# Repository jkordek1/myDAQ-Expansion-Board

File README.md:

# myDAQ Expansion Board

 Expansion board for NI myDAQ Student Data Acquisition Device, developed in 2022 for students studying at Zagreb university of applied sciences.
 It enables quick and easy .VI development without the need of connecting different modules via breadboard and jumpers.
 
 ## Features
 - Push buttons
 - Toggle switches
 - LEDs
 - BCD decoder for seven-segment display
 - L298n H-bridge used for powering two DC motors or one stepper motor
 - ACS712ELCTR-05B-T current sense IC for motor current measurement
 - External power supply for DC motors
 - Potentiometer
 - Light dependent resistor

## Images

## Project folder structure
    .
    ├── ...
    ├── 3DPrint                 # Files for 3D printing
    ├── Images                  # Images of the project
    ├── KiCADFiles              # Main folder
    │   ├── 3d models           # 3d models of components
    │   ├── Datasheet           # Datasheet collection
    │   ├── Graphics            # Custom graphics for PCB
    │   ├── gerber              # gerber output folder
    │   ├── myDAQExpansionBoard # Main folder for KiCAD files
    │   └── Schematic.pdf       # Project schematic
    └── ...

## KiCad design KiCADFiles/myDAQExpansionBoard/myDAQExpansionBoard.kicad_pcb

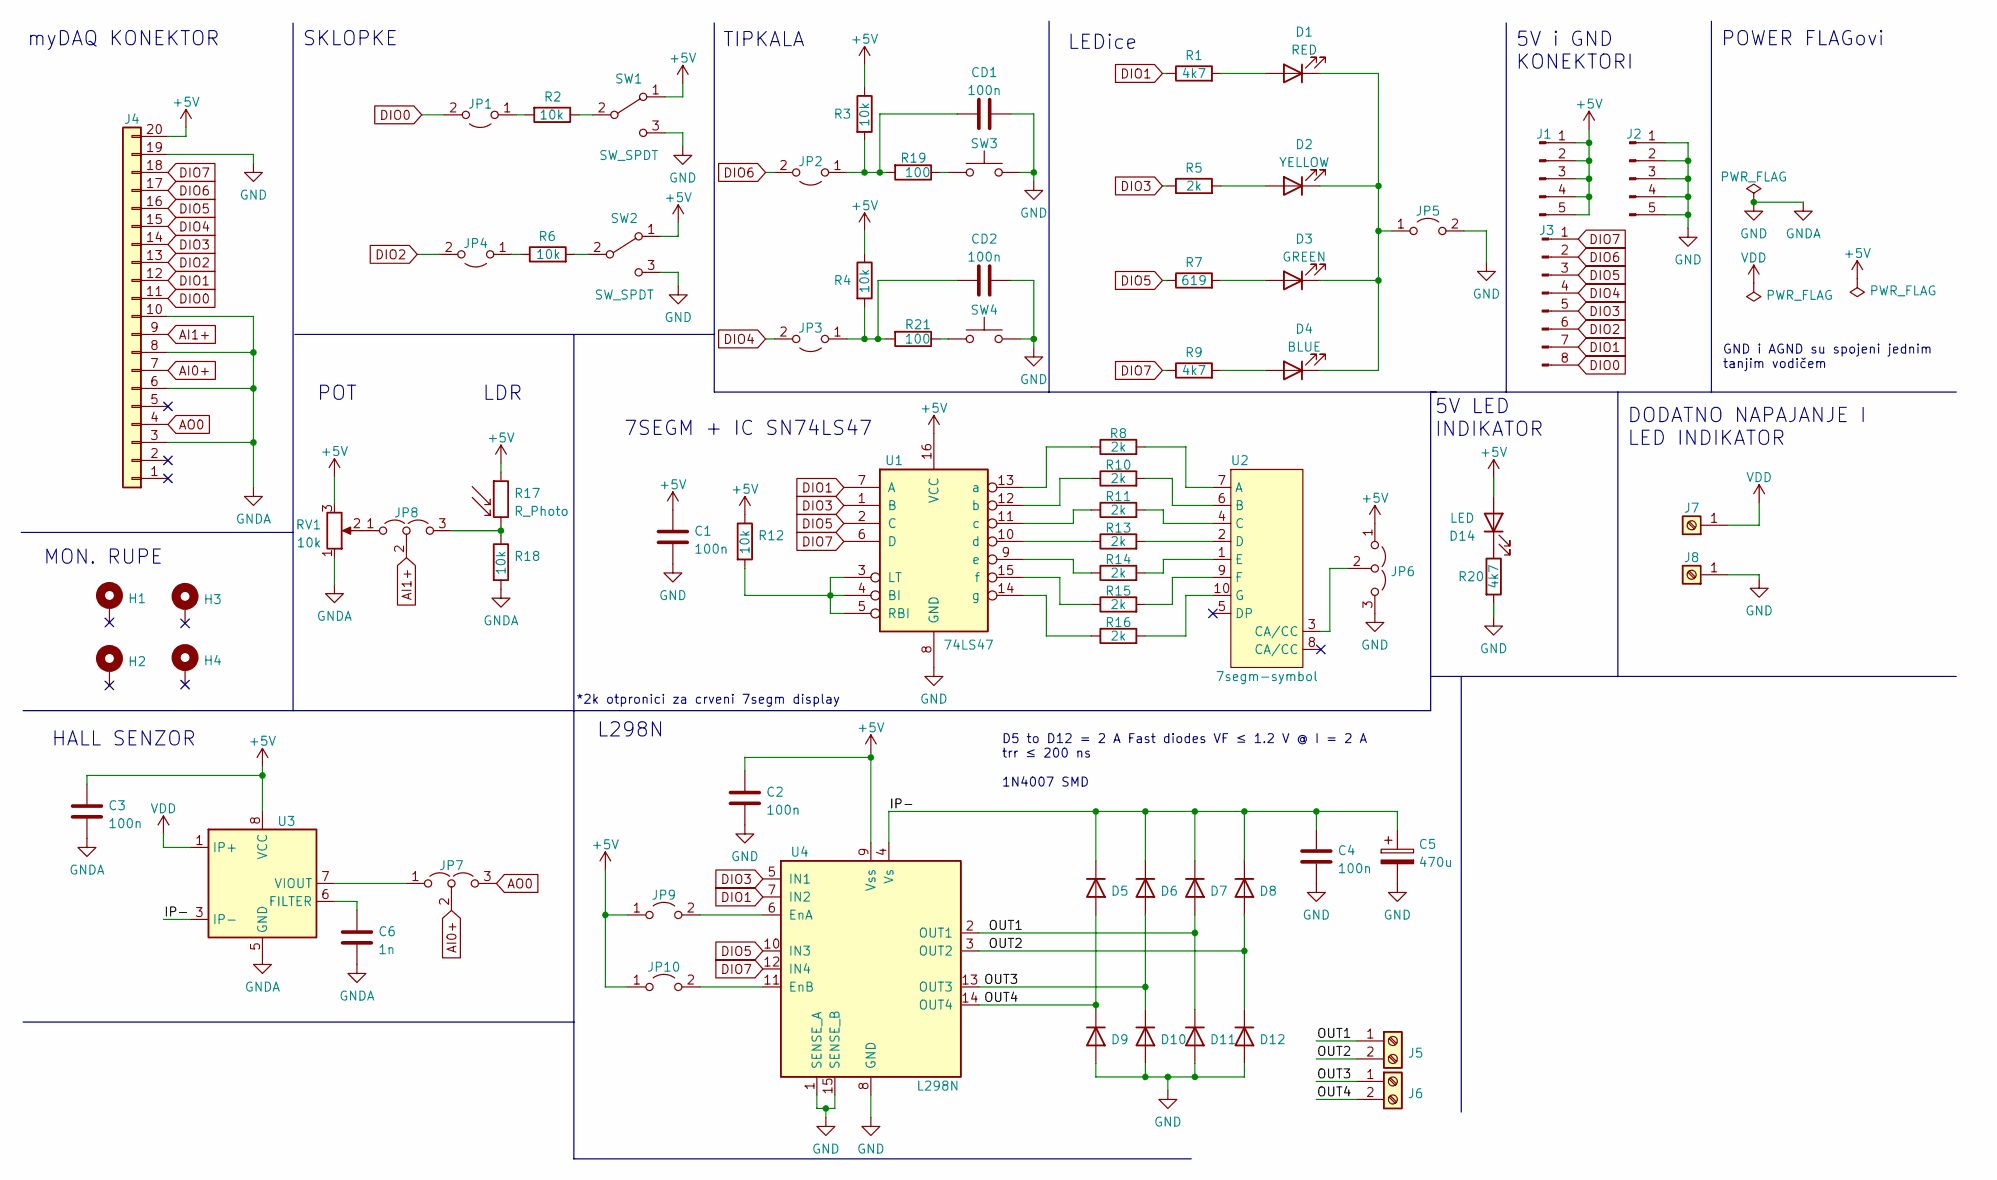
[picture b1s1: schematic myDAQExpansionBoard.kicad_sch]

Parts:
C1, C2, C3, C4: 100n; C_0603_1608Metric
C5: 470u; C_Radial_D10.0mm_H16.0mm_P5.00mm
C6: 1n; C_0603_1608Metric
CD1, CD2: 100n; C_0805_2012Metric
D1: RED; LED_D5.0mm
D2: YELLOW; LED_D5.0mm
D3: GREEN; LED_D5.0mm
D4: BLUE; LED_D5.0mm
D5, D6, D7, D8, D9, D10, D11, D12: 1N4007; D_SMA
D14: LED; LED_1206_3216Metric
H1, H2, H3, H4: MountingHole_Pad; MountingHole_3.2mm_M3_ISO7380_Pad
J1, J2: Conn_01x05_Male; PinHeader_1x05_P2.54mm_Vertical
J3: Conn_01x08_Male; PinHeader_1x08_P2.54mm_Vertical
J4: OSTV7XX3151
J5, J6: Screw_Terminal_01x02; TerminalBlock_Phoenix_MKDS-1,5-2-5.08_1x02_P5.08mm_Horizont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
J7: Screw_Terminal_01x01; DELTRON 4mm banana socket - red
J8: Screw_Terminal_01x01; DELTRON 4mm banana socket - black
JP1, JP2, JP3, JP4, JP5, JP9, JP10: Jumper_2_Open; PinHeader_1x02_P2.54mm_jumper
JP6, JP7, JP8: Jumper_3_Open; PinHeader_1x03_P2.54mm_Vertical_jumper
R1, R9, R20: 4k7; R_0603_1608Metric
R2, R3, R4, R6, R12, R18: 10k; R_0603_1608Metric
R5, R8, R10, R11, R13, R14, R15, R16: 2k; R_0603_1608Metric
R7: 619; R_0603_1608Metric
R17: R_Photo; R_LDR_5.1x4.3mm_P3.4mm_Vertical
R19, R21: 100; R_0603_1608Metric
RV1: 10k; PTV09A-4225F-B502
SW1, SW2: SW_SPDT; EG1271A
SW3, SW4: SW_Push; Omron_B3F-12x12mm
U1: 74LS47; DIP-16_W7.62mm
U2: 7segm-symbol; 7segm-SA52
U3: ACS712xLCTR-05B; SOIC-8_3.9x4.9mm_P1.27mm
U4: L298N; L298n

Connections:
+5V: C1.1, C2.1, C3.1, D14.2 (A), J1.1, J1.2, J1.3, J1.4, J1.5, J4.20, JP6.1 (A), JP9.1 (A), JP10.1 (A), R3.1, R4.1, R12.1, R17.1, RV1.3, SW1.1 (A), SW2.1 (A), U1.16 (VCC), U3.8 (VCC), U4.9 (Vss)
/IP-: C4.1, C5.1, D5.1 (K), D6.1 (K), D7.1 (K), D8.1 (K), U3.3 (IP-), U3.4 (IP-), U4.4 (Vs)
/OUT1: D7.2 (A), D11.1 (K), J5.1, U4.2 (OUT1)
/OUT2: D8.2 (A), D12.1 (K), J5.2, U4.3 (OUT2)
/OUT3: D6.2 (A), D10.1 (K), J6.1, U4.13 (OUT3)
/OUT4: D5.2 (A), D9.1 (K), J6.2, U4.14 (OUT4)
AI0+: J4.7, JP7.2 (C)
AI1+: J4.9, JP8.2 (C)
AO0: J4.4, JP7.3 (B)
DIO0: J3.8, J4.11, JP1.2 (B)
DIO1: J3.7, J4.12, R1.1, U1.7 (A), U4.7 (IN2)
DIO2: J3.6, J4.13, JP4.2 (B)
DIO3: J3.5, J4.14, R5.1, U1.1 (B), U4.5 (IN1)
DIO4: J3.4, J4.15, JP3.2 (B)
DIO5: J3.3, J4.16, R7.1, U1.2 (C), U4.10 (IN3)
DIO6: J3.2, J4.17, JP2.2 (B)
DIO7: J3.1, J4.18, R9.1, U1.6 (D), U4.12 (IN4)
GND: C1.2, C2.2, C3.2, C4.2, C5.2, C6.2, CD1.2, CD2.2, D9.2 (A), D10.2 (A), D11.2 (A), D12.2 (A), J2.1, J2.2, J2.3, J2.4, J2.5, J4.3, J4.6, J4.8, J4.10, J4.19, J8.1, JP5.2 (B), JP6.3 (B), R18.2, R20.2, RV1.1, SW1.3 (C), SW2.3 (C), SW3.2, SW4.2, U1.8 (GND), U3.5 (GND), U4.1 (SENSE_A), U4.8 (GND), U4.15 (SENSE_B)
unnamed: C6.1, U3.6 (FILTER)
unnamed: CD1.1, JP2.1 (A), R3.2, R19.2
unnamed: CD2.1, JP3.1 (A), R4.2, R21.2
unnamed: D1.1 (K), D2.1 (K), D3.1 (K), D4.1 (K), JP5.1 (A)
unnamed: D1.2 (A), R1.2
unnamed: D2.2 (A), R5.2
unnamed: D3.2 (A), R7.2
unnamed: D4.2 (A), R9.2
unnamed: D14.1 (K), R20.1
unnamed: JP1.1 (A), R2.2
unnamed: JP4.1 (A), R6.1
unnamed: JP6.2 (C), U2.3 (CA/CC)
unnamed: JP7.1 (A), U3.7 (VIOUT)
unnamed: JP8.1 (A), RV1.2
unnamed: JP8.3 (B), R17.2, R18.1
unnamed: JP9.2 (B), U4.6 (EnA)
unnamed: JP10.2 (B), U4.11 (EnB)
unnamed: R2.1, SW1.2 (B)
unnamed: R6.2, SW2.2 (B)
unnamed: R8.1, U1.13 (a)
unnamed: R8.2, U2.7 (A)
unnamed: R10.1, U1.12 (b)
unnamed: R10.2, U2.6 (B)
unnamed: R11.1, U1.11 (c)
unnamed: R11.2, U2.4 (C)
unnamed: R12.2, U1.3 (LT), U1.4 (BI), U1.5 (RBI)
unnamed: R13.1, U1.10 (d)
unnamed: R13.2, U2.2 (D)
unnamed: R14.1, U1.9 (e)
unnamed: R14.2, U2.1 (E)
unnamed: R15.1, U1.15 (f)
unnamed: R15.2, U2.9 (F)
unnamed: R16.1, U1.14 (g)
unnamed: R16.2, U2.10 (G)
unnamed: R19.1, SW3.1
unnamed: R21.1, SW4.1
VDD: J7.1, U3.1 (IP+), U3.2 (IP+)

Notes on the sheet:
myDAQ KONEKTOR
LEDice
5V LED INDIKATOR
*2k otpronici za crveni 7segm display
D5 to D12 = 2 A Fast diodes VF ≤ 1.2 V @ I = 2 A trr ≤ 200 ns 1N4007 SMD
5V i GND KONEKTORI
7SEGM + IC SN74LS47
POT
HALL SENZOR
POWER FLAGovi
L298N
MON. RUPE
TIPKALA
SKLOPKE
DODATNO NAPAJANJE I LED INDIKATOR
GND i AGND su spojeni jednim tanjim vodičem
LDR

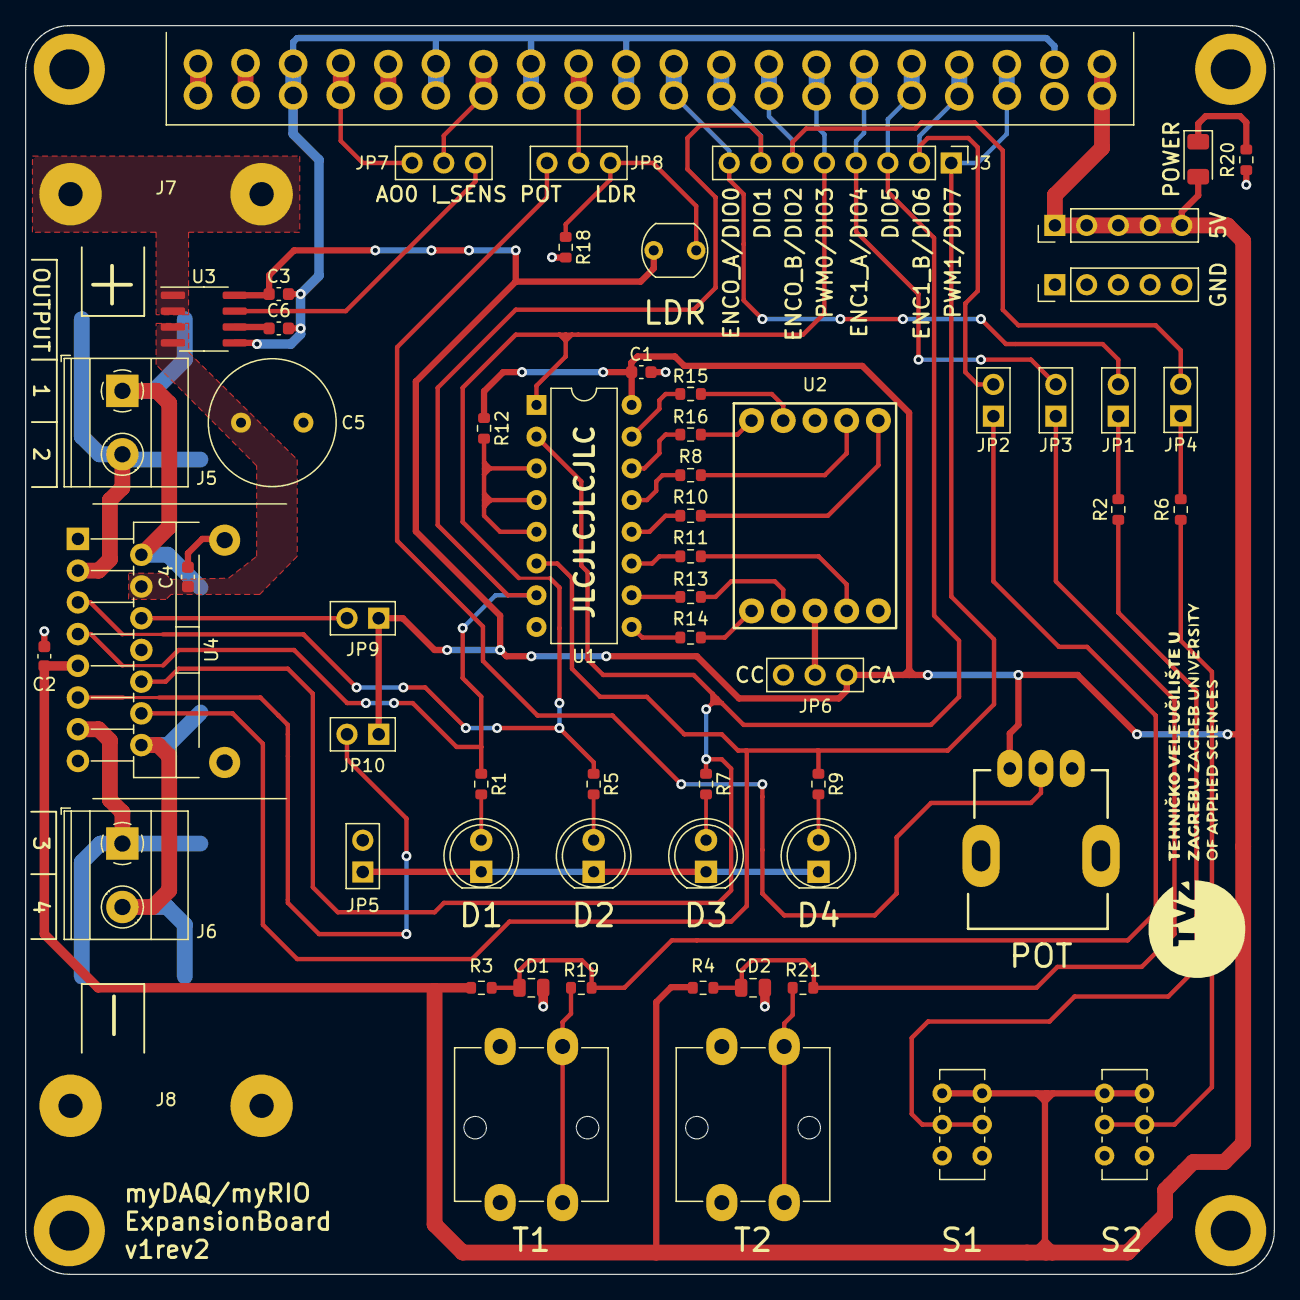
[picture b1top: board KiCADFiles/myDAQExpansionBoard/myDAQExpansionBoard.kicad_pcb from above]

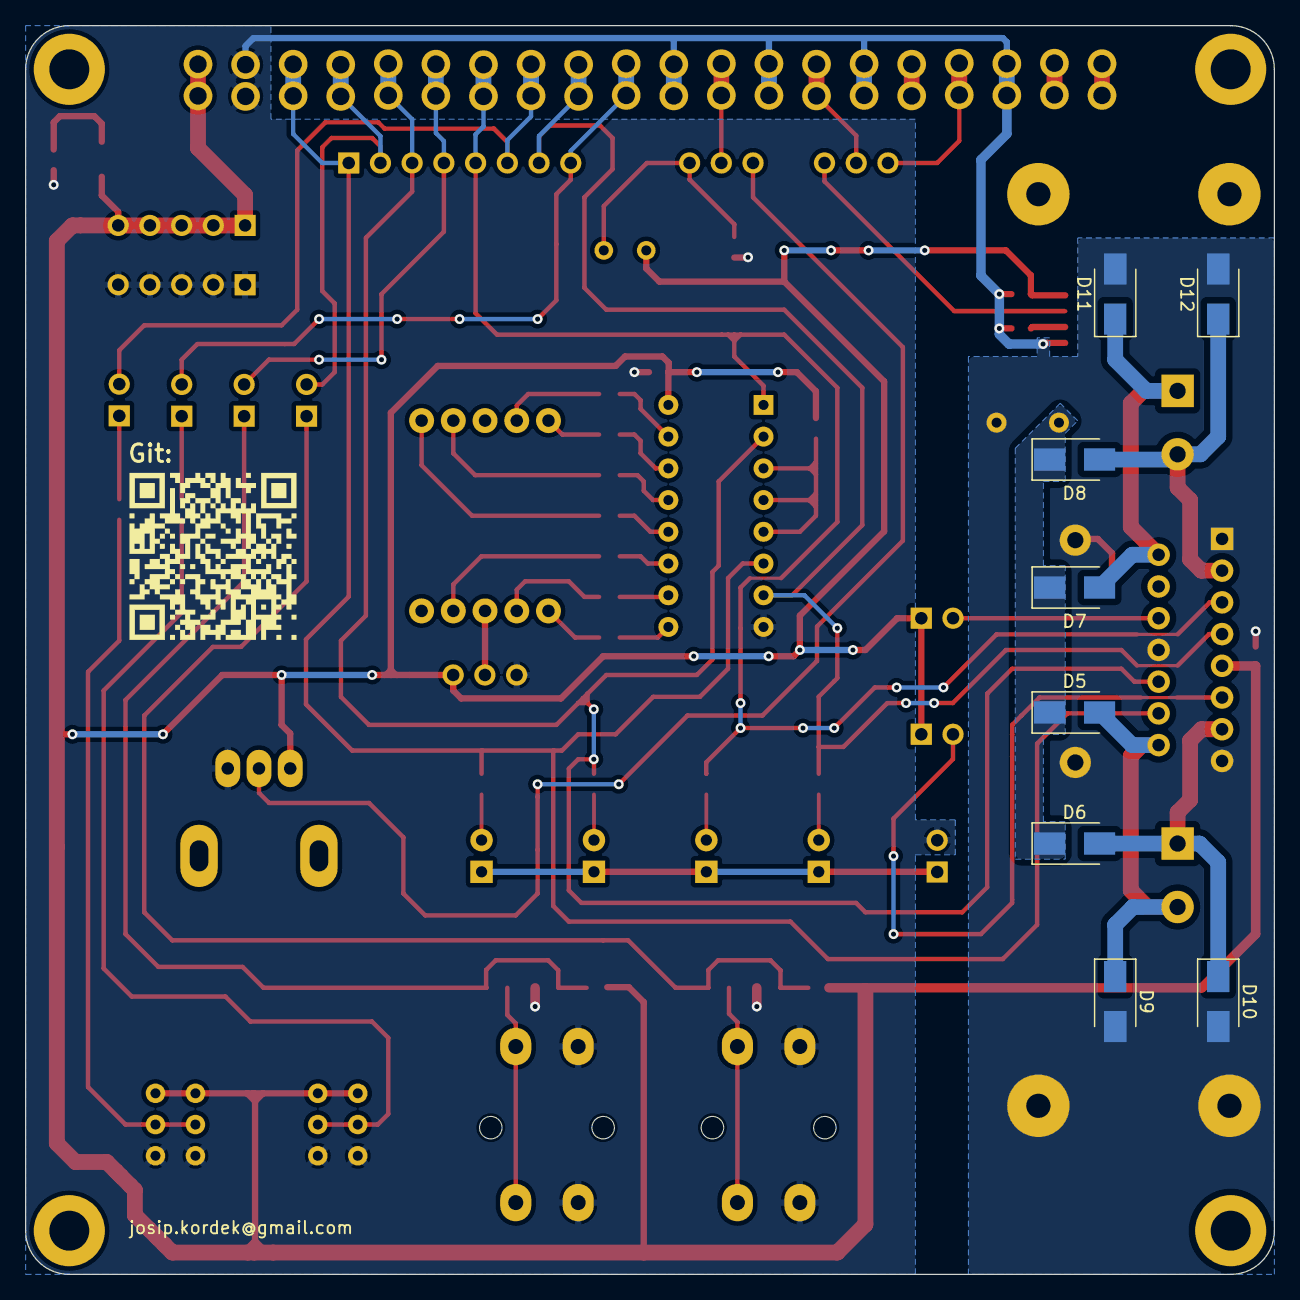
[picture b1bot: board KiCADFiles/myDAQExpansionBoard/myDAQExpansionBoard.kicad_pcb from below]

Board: 2 copper layers, 100.0 x 100.0 mm, 73 parts (8 on the bottom side), 55 nets.

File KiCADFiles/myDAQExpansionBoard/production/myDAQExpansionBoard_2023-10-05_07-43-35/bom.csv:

Designator,Footprint,Quantity,Value,LCSC Part #
"C1, C2, C3, C4",0603,4,100n,
C5,C_Radial_D10.0mm_H16.0mm_P5.00mm,1,470u,
C6,0603,1,1n,
"CD1, CD2",0805,2,100n,
D1,LED_D5.0mm,1,RED,
"D10, D11, D12, D5, D6, D7, D8, D9",D_SMA,8,1N4007,
D14,1206,1,LED,
D2,LED_D5.0mm,1,YELLOW,
D3,LED_D5.0mm,1,GREEN,
D4,LED_D5.0mm,1,BLUE,
"H1, H2, H3, H4",MountingHole_3.2mm_M3_ISO7380_Pad,4,MountingHole_Pad,
"J1, J2",PinHeader_1x05_P2.54mm_Vertical,2,Conn_01x05_Male,
J3,PinHeader_1x08_P2.54mm_Vertical,1,Conn_01x08_Male,
J4,OSTV7XX3151,1,OSTV7XX3151,
"J5, J6","TerminalBlock_Phoenix_MKDS-1,5-2-5.08_1x02_P5.08mm_Horizontal",2,Screw_Terminal_01x02,
J7,DELTRON 4mm banana socket - red,1,Screw_Terminal_01x01,
J8,DELTRON 4mm banana socket - black,1,Screw_Terminal_01x01,
"JP1, JP10, JP2, JP3, JP4, JP5, JP9",PinHeader_1x02_P2.54mm_jumper,7,Jumper_2_Open,
"JP6, JP7, JP8",PinHeader_1x03_P2.54mm_Vertical_jumper,3,Jumper_3_Open,
"R1, R20, R9",0603,3,4k7,
"R10, R11, R13, R14, R15, R16, R5, R8",0603,8,2k,
"R12, R18, R2, R3, R4, R6",0603,6,10k,
R17,R_LDR_5.1x4.3mm_P3.4mm_Vertical,1,R_Photo,
"R19, R21",0603,2,100,
R7,0603,1,619,
RV1,PTV09A-4225F-B502,1,10k,
"SW1, SW2",EG1271A,2,SW_SPDT,
"SW3, SW4",Omron_B3F-12x12mm,2,SW_Push,
U1,DIP-16_W7.62mm,1,74LS47,
U2,7segm-SA52,1,7segm-symbol,
U3,SOIC-8_3.9x4.9mm_P1.27mm,1,ACS712xLCTR-05B,
U4,L298n,1,L298N,

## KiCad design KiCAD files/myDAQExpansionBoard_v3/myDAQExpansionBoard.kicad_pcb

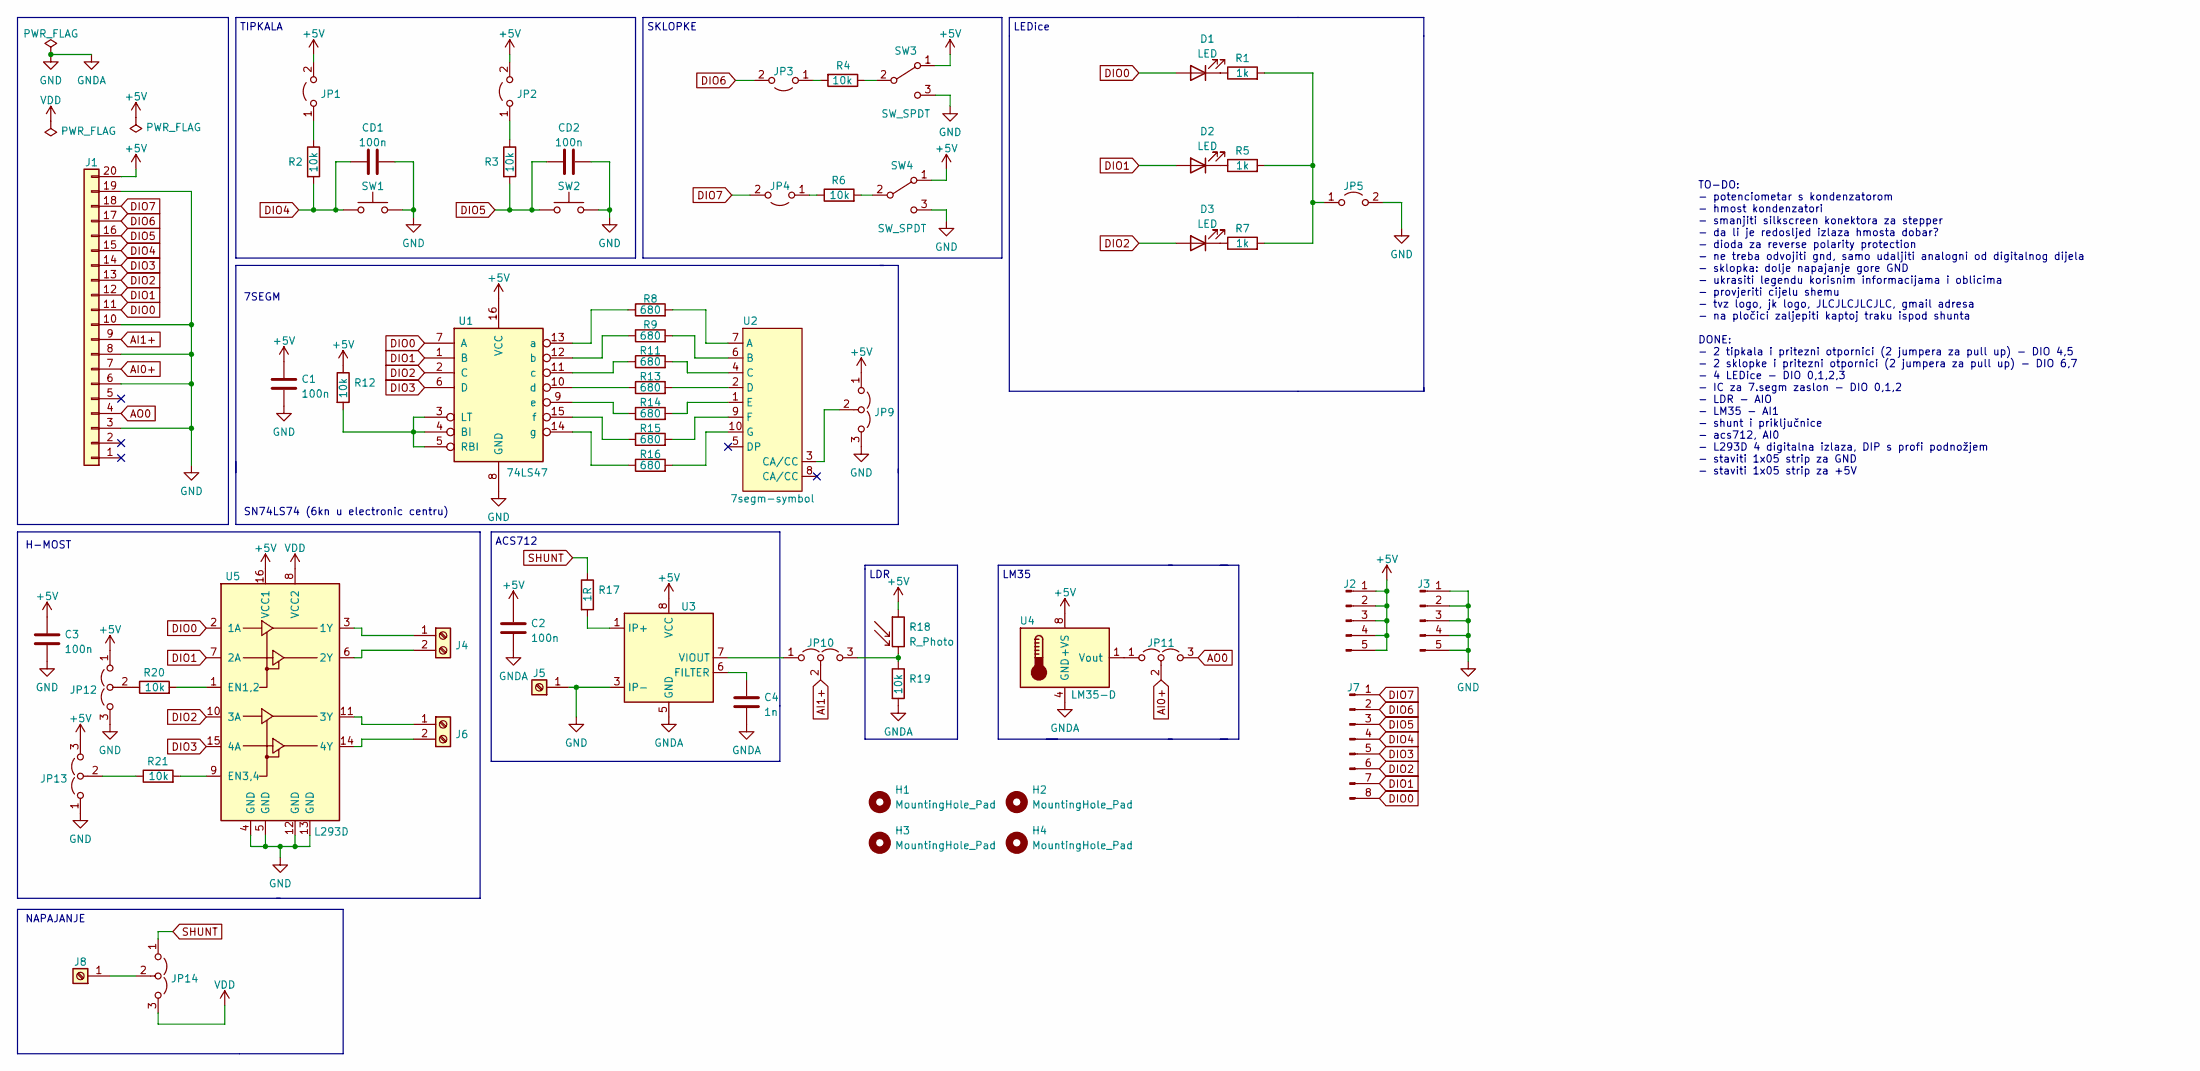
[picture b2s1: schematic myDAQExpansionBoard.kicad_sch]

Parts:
C1, C2, C3: 100n; C_0603_1608Metric
C4: 1n; C_0603_1608Metric
CD1, CD2: 100n; C_0603_1608Metric
D1, D2, D3: LED; LED_D5.0mm
H1, H2, H3, H4: MountingHole_Pad; MountingHole_3.2mm_M3
J1: OSTV7XX3151
J2, J3: Conn_01x05_Male; PinHeader_1x05_P2.54mm_Vertical
J4, J6: Screw_Terminal_01x02; TerminalBlock_Phoenix_MKDS-1,5-2-5.08_1x02_P5.08mm_Horizont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
J5: Screw_Terminal_01x01; DELTRON 4mm banana socket - black
J7: Conn_01x08_Male; PinHeader_1x08_P2.54mm_Vertical
J8: Screw_Terminal_01x01; DELTRON 4mm banana socket - red
JP1, JP2, JP3, JP4, JP5: Jumper_2_Open; PinHeader_1x02_P2.54mm_Vertical
JP9, JP10, JP11, JP12, JP13, JP14: Jumper_3_Open; PinHeader_1x03_P2.54mm_Vertical
R1, R5, R7: 1k; R_0603_1608Metric
R2, R3, R4, R6, R12, R19, R20, R21: 10k; R_0603_1608Metric
R8, R9, R11, R13, R14, R15, R16: 680; R_0603_1608Metric
R17: 1R; R_Axial_Power_L60.0mm_W14.0mm_P71.12mm
R18: R_Photo; R_LDR_5.1x4.3mm_P3.4mm_Vertical
SW1, SW2: SW_Push; Omron_B3F-12x12mm
SW3, SW4: SW_SPDT; we01014042
U1: 74LS47; DIP-16_W7.62mm
U2: 7segm-symbol; 7segm-SA52
U3: ACS712xLCTR-05B; SOIC-8_3.9x4.9mm_P1.27mm
U4: LM35-D; SOIC-8_3.9x4.9mm_P1.27mm
U5: L293D; DIP-16_W7.62mm

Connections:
+5V: C1.1, C2.1, C3.1, J1.20, J2.1, J2.2, J2.3, J2.4, J2.5, JP1.2 (B), JP2.2 (B), JP9.1 (A), JP12.1 (A), JP13.3 (B), R12.1, R18.1, SW3.1 (A), SW4.1 (A), U1.16 (VCC), U3.8 (VCC), U4.8 (+VS), U5.16 (VCC1)
AI0+: J1.7, JP11.2 (C)
AI1+: J1.9, JP10.2 (C)
AO0: J1.4, JP11.3 (B)
DIO0: D1.2 (A), J1.11, J7.8, U1.7 (A), U5.2 (1A)
DIO1: D2.2 (A), J1.12, J7.7, U1.1 (B), U5.7 (2A)
DIO2: D3.2 (A), J1.13, J7.6, U1.2 (C), U5.10 (3A)
DIO3: J1.14, J7.5, U1.6 (D), U5.15 (4A)
DIO4: CD1.1, J1.15, J7.4, R2.2, SW1.1
DIO5: CD2.1, J1.16, J7.3, R3.2, SW2.1
DIO6: J1.17, J7.2, JP3.2 (B)
DIO7: J1.18, J7.1, JP4.2 (B)
GND: C1.2, C2.2, C3.2, C4.2, CD1.2, CD2.2, J1.3, J1.6, J1.8, J1.10, J1.19, J3.1, J3.2, J3.3, J3.4, J3.5, J5.1, JP5.2 (B), JP9.3 (B), JP12.3 (B), JP13.1 (A), R19.2, SW1.2, SW2.2, SW3.3 (C), SW4.3 (C), U1.8 (GND), U3.3 (IP-), U3.4 (IP-), U3.5 (GND), U4.4 (GND), U5.4 (GND), U5.5 (GND), U5.12 (GND), U5.13 (GND)
unnamed: C4.1, U3.6 (FILTER)
unnamed: D1.1 (K), R1.1
unnamed: D2.1 (K), R5.1
unnamed: D3.1 (K), R7.1
unnamed: J4.1, U5.3 (1Y)
unnamed: J4.2, U5.6 (2Y)
unnamed: J6.1, U5.11 (3Y)
unnamed: J6.2, U5.14 (4Y)
unnamed: J8.1, JP14.2 (C)
unnamed: JP1.1 (A), R2.1
unnamed: JP2.1 (A), R3.1
unnamed: JP3.1 (A), R4.2
unnamed: JP4.1 (A), R6.1
unnamed: JP5.1 (A), R1.2, R5.2, R7.2
unnamed: JP9.2 (C), U2.3 (CA/CC)
unnamed: JP10.1 (A), U3.7 (VIOUT)
unnamed: JP10.3 (B), R18.2, R19.1
unnamed: JP11.1 (A), U4.1 (Vout)
unnamed: JP12.2 (C), R20.1
unnamed: JP13.2 (C), R21.1
unnamed: R4.1, SW3.2 (B)
unnamed: R6.2, SW4.2 (B)
unnamed: R8.1, U1.13 (a)
unnamed: R8.2, U2.7 (A)
unnamed: R9.1, U1.12 (b)
unnamed: R9.2, U2.6 (B)
unnamed: R11.1, U1.11 (c)
unnamed: R11.2, U2.4 (C)
unnamed: R12.2, U1.3 (LT), U1.4 (BI), U1.5 (RBI)
unnamed: R13.1, U1.10 (d)
unnamed: R13.2, U2.2 (D)
unnamed: R14.1, U1.9 (e)
unnamed: R14.2, U2.1 (E)
unnamed: R15.1, U1.15 (f)
unnamed: R15.2, U2.9 (F)
unnamed: R16.1, U1.14 (g)
unnamed: R16.2, U2.10 (G)
unnamed: R17.2, U3.1 (IP+), U3.2 (IP+)
unnamed: R20.2, U5.1 (EN1,2)
unnamed: R21.2, U5.9 (EN3,4)
SHUNT: JP14.1 (A), R17.1
VDD: JP14.3 (B), U5.8 (VCC2)

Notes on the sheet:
TO-DO: - potenciometar s kondenzatorom - hmost kondenzatori - smanjiti silkscreen konektora za stepper - da li je redosljed izlaza hmosta dobar? - dioda za reverse polarity protection - ne treba odvojiti gnd, samo udaljiti analogni od digitalnog dijela - sklopka: dolje napajanje gore GND - ukrasiti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
SN74LS74 (6kn u electronic centru)
LM35
7SEGM
ACS712
NAPAJANJE
TIPKALA
H-MOST
LDR
LEDice
SKLOPKE

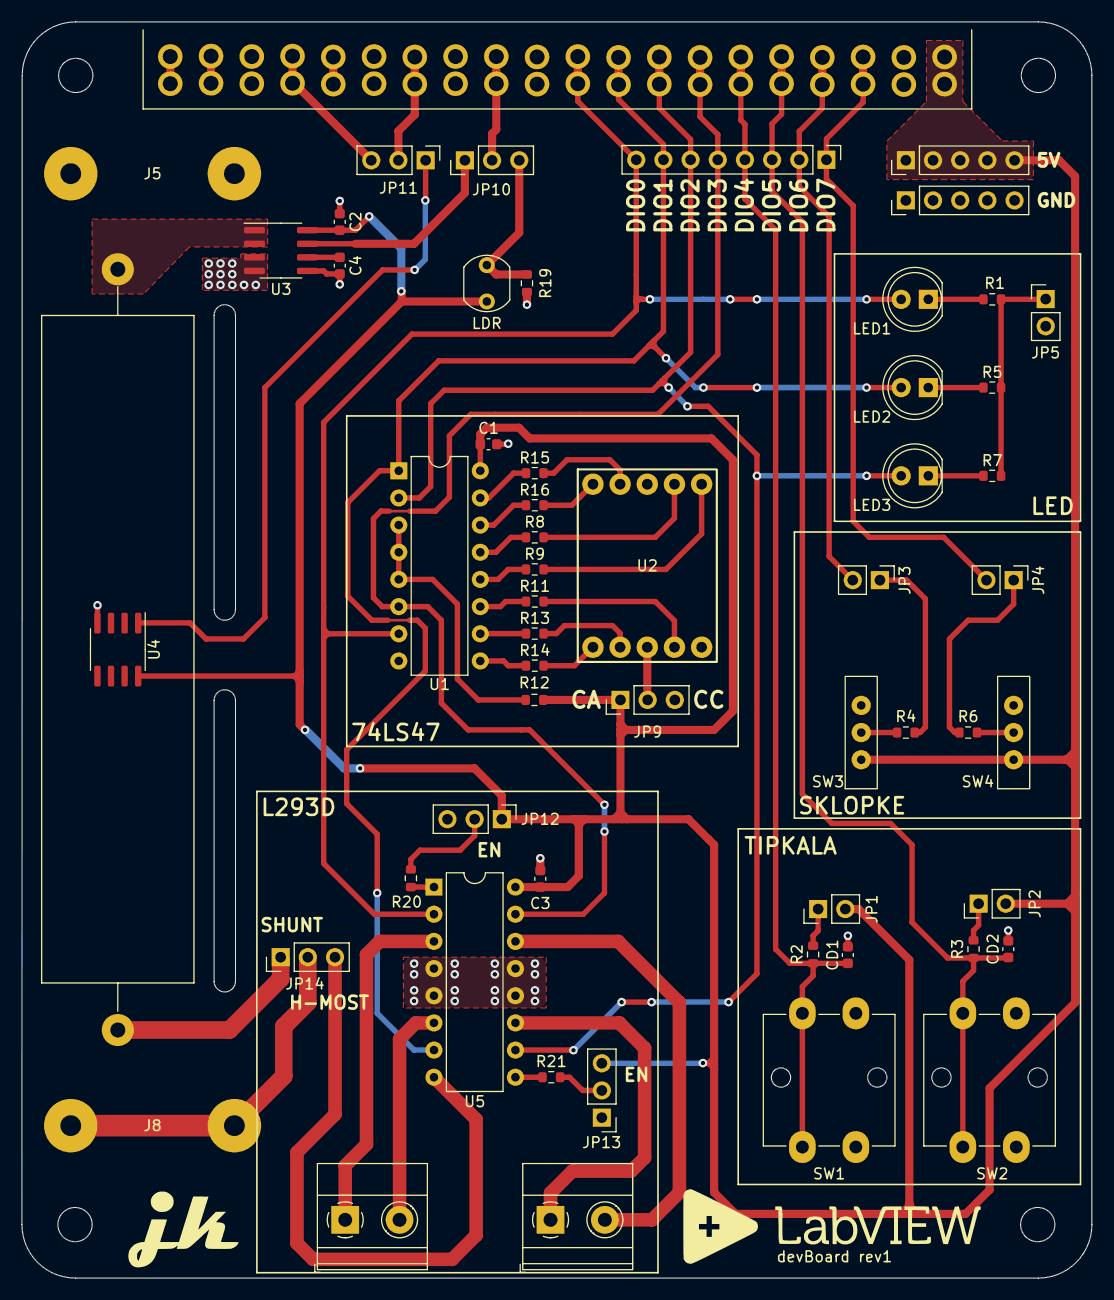
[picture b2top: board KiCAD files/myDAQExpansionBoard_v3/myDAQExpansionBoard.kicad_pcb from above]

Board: 2 copper layers, 100.0 x 117.4 mm, 61 parts (0 on the bottom side), 55 nets.

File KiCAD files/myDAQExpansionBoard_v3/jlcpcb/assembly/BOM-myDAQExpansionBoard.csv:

Comment,Designator,Footprint,LCSC
680,R11,R_0603_1608Metric,
MountingHole_Pad,H1,MountingHole_3.2mm_M3_Pad_Via,
LED,D4,LED_D5.0mm,
SW_Push,SW1,Omron_B3F-12x12mm,
100n,CD2,C_0603_1608Metric,
Jumper_2_Open,JP5,PinHeader_1x02_P2.54mm_Vertical,
100n,C3,C_0603_1608Metric,
SW_SPDT,SW4,we01014042,
Jumper_3_Open,JP10,PinHeader_1x03_P2.54mm_Vertical,
10k,R3,R_0603_1608Metric,
Jumper_2_Open,JP1,PinHeader_1x02_P2.54mm_Vertical,
Conn_01x05_Male,J2,PinHeader_1x05_P2.54mm_Vertical,
SW_Push,SW2,Omron_B3F-12x12mm,
Jumper_3_Open,JP14,PinHeader_1x03_P2.54mm_Vertical,
Screw_Terminal_01x02,J6,"TerminalBlock_Phoenix_MKDS-1,5-2-5.08_1x02_P5.08mm_Horizontal",
1n,C4,C_0603_1608Metric,
LED,D2,LED_D5.0mm,
10k,R21,R_0603_1608Metric,
680,R13,R_0603_1608Metric,
680,R8,R_0603_1608Metric,
MountingHole_Pad,H4,MountingHole_3.2mm_M3_Pad_Via,
SW_SPDT,SW3,we01014042,
Jumper_3_Open,JP12,PinHeader_1x03_P2.54mm_Vertical,
Jumper_2_Open,JP2,PinHeader_1x02_P2.54mm_Vertical,
OSTV7XX3151,J1,OSTV7XX3151,
ACS712xLCTR-05B,U3,SOIC-8_3.9x4.9mm_P1.27mm,
Jumper_3_Open,JP9,PinHeader_1x03_P2.54mm_Vertical,
74LS47,U1,DIP-16_W7.62mm,
R_Photo,R18,R_LDR_5.1x4.3mm_P3.4mm_Vertical,
Jumper_2_Open,JP3,PinHeader_1x02_P2.54mm_Vertical,
10k,R20,R_0603_1608Metric,
100n,CD1,C_0603_1608Metric,
1k,R1,R_0603_1608Metric,
100n,C1,C_0603_1608Metric,
L293D,U5,DIP-16_W7.62mm,
7segm-symbol,U2,7segm-SA52,
MountingHole_Pad,H2,MountingHole_3.2mm_M3_Pad_Via,
Jumper_3_Open,JP13,PinHeader_1x03_P2.54mm_Vertical,
10k,R4,R_0603_1608Metric,
100n,C2,C_0603_1608Metric,
Jumper_3_Open,JP11,PinHeader_1x03_P2.54mm_Vertical,
LM35-D,U4,SOIC-8_3.9x4.9mm_P1.27mm,
LED,D1,LED_D5.0mm,
MountingHole_Pad,H3,MountingHole_3.2mm_M3_Pad_Via,
Screw_Terminal_01x01,J8,DELTRON 4mm banana socket - red,
680,R14,R_0603_1608Metric,
Jumper_2_Open,JP4,PinHeader_1x02_P2.54mm_Vertical,
1R,R17,R_Axial_Power_L60.0mm_W14.0mm_P71.12mm,
680,R15,R_0603_1608Metric,
10k,R12,R_0603_1608Metric,
1k,R10,R_0603_1608Metric,
10k,R6,R_0603_1608Metric,
680,R16,R_0603_1608Metric,
LED,D3,LED_D5.0mm,
1k,R5,R_0603_1608Metric,
10k,R19,R_0603_1608Metric,
Screw_Terminal_01x01,J5,DELTRON 4mm banana socket - black,
Conn_01x05_Male,J3,PinHeader_1x05_P2.54mm_Vertical,
Conn_01x08_Male,J7,PinHeader_1x08_P2.54mm_Vertical,
680,R9,R_0603_1608Metric,
1k,R7,R_0603_1608Metric,
10k,R2,R_0603_1608Metric,
Screw_Terminal_01x02,J4,"TerminalBlock_Phoenix_MKDS-1,5-2-5.08_1x02_P5.08mm_Horizontal",

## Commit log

2022-07-23 Initial release
2022-07-24 schematic first revision
2022-07-26 layout
2022-09-06 update_v3
2022-09-14 Update fp-info-cache
2022-09-15 Inital release, board v1
2022-09-15 Initial release, board v1
2022-09-15 render image
2022-10-04 BOMv1
2022-11-24 Added resistor for RC circuit
2022-12-19 v1rev2
2023-04-17 release badge
